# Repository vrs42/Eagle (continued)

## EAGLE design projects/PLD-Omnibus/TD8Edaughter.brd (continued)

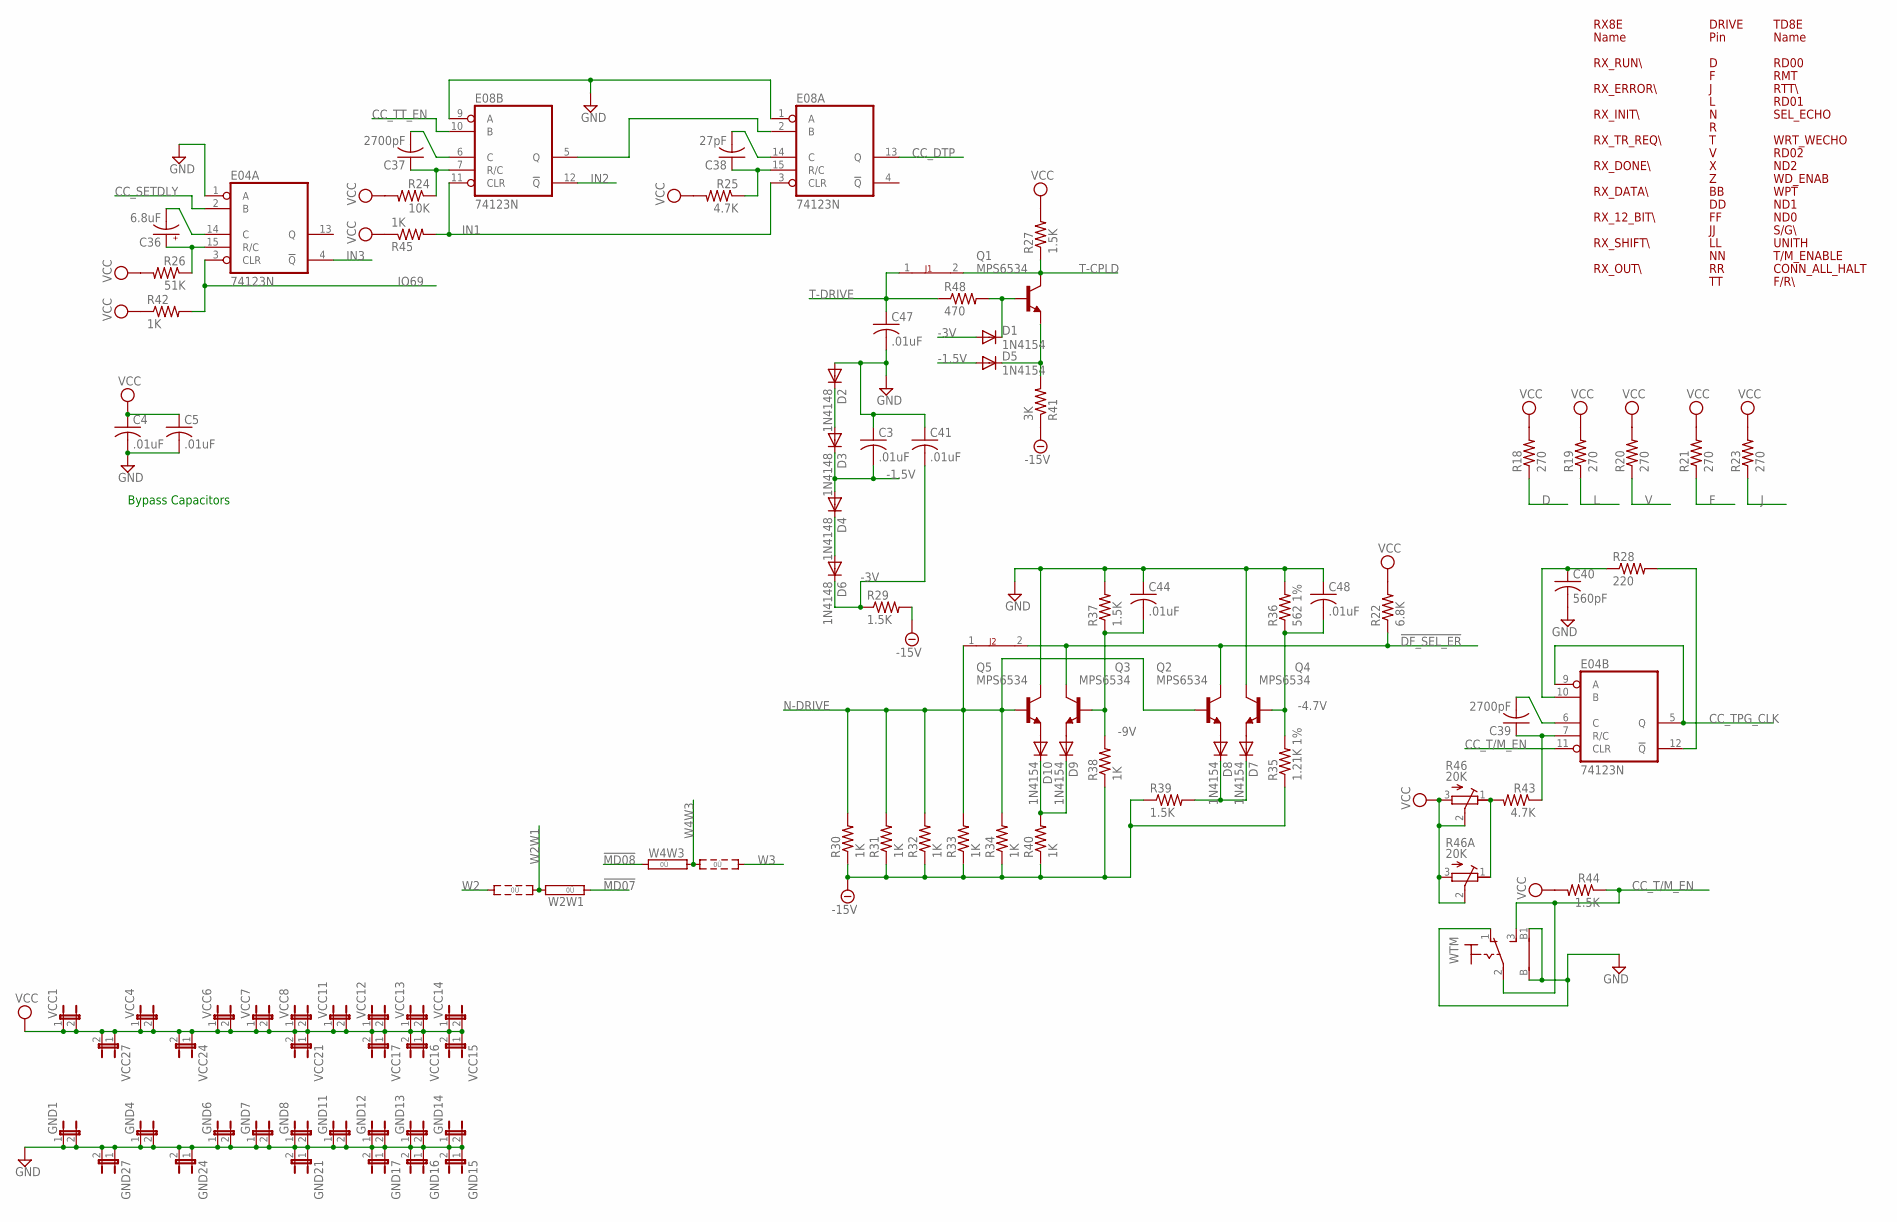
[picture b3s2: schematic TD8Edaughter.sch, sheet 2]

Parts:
C3, C4, C5, C41, C44, C47, C48: .01uF; C050-025X075
C36: 6.8uF; E12-8
C37, C39: 2700pF; C102-043X133
C38: 27pF; C050-025X075
C40: 560pF; C075-032X103
D1, D5, D7, D8, D9, D10: 1N4154; DO35-10
D2, D3, D4, D6: 1N4148; DO35-10
E04, E08: 74123N; DIL16
GND1, GND4, GND6, GND7, GND8, GND11, GND12, GND13, GND14, GND15, GND16, GND17, GND21, GND24, GND27: JP1E; JP1
J1, J2: JUMPER-NC; NC1
Q1, Q2, Q3, Q4, Q5: MPS6534; TO5
R18, R19, R20, R21, R23: 270; 0207/10
R22: 6.8K; 0207/10
R24: 10K; 0207/10
R25, R43: 4.7K; 0207/10
R26: 51K; 0207/10
R27, R29, R37, R39, R44: 1.5K; 0207/10
R28: 220; 0207/10
R30, R31, R32, R33, R34, R38, R40, R42, R45: 1K; 0207/10
R35: 1.21K 1%; 0207/15
R36: 562 1%; 0207/15
R41: 3K; 0207/10
R46: 20K; 3006Y
R46A: 20K; RTRIM3006P
R48: 470; 0207/10
VCC1, VCC4, VCC6, VCC7, VCC8, VCC11, VCC12, VCC13, VCC14, VCC15, VCC16, VCC17, VCC21, VCC24, VCC27: JP1E; JP1
W2W1, W4W3: 0R2; 0R2/10
WTM: 9070-1W

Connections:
!CC_TPG_CLK: C40.1, E04.10 (B), R28.1
!DF_SEL_ER: J2.2, Q2.3 (C), Q3.3 (C), R22.1; also elsewhere on the board
!MD07: W2W1.1; also elsewhere on the board
!MD08: W4W3.1; also elsewhere on the board
-1.5V: C3.2, D3.C, D4.A, D5.A
-3V: C41.2, D1.A, D6.C, R29.1
-4.7V: C48.2, Q4.2 (B), R35.2, R36.1
-9V: C44.2, Q3.2 (B), R37.1, R38.2
-15V: R29.2, R30.1, R31.1, R32.1, R33.1, R34.1, R35.1, R38.1, R39.1, R40.1, R41.1; also elsewhere on the board
CC_DTP: E08.13 (Q); also elsewhere on the board
CC_SETDLY: E04.2 (B); also elsewhere on the board
CC_T/M_EN: E04.11 (CLR), R44.1, WTM.2, WTM.3 (S); also elsewhere on the board
CC_TPG_CLK: E04.5 (Q), E04.9 (A); also elsewhere on the board
CC_TT_EN: E08.10 (B); also elsewhere on the board
D: R18.1; also elsewhere on the board
F: R21.1; also elsewhere on the board
GND: C3.1, C4.2, C5.2, C40.2, C41.1, C44.1, C47.2, C48.1, D2.A, E04.1 (A), E04.8 (GND), E08.1 (A), E08.8 (GND), E08.9 (A), GND1.1, GND1.2, GND4.1, GND4.2, GND6.1, GND6.2, GND7.1, GND7.2, GND8.1, GND8.2, GND11.1, GND11.2, GND12.1, GND12.2, GND13.1, GND13.2, GND14.1, GND14.2, GND15.1, GND15.2, GND16.1, GND16.2, GND17.1, GND17.2, GND21.1, GND21.2, GND24.1, GND24.2, GND27.1, GND27.2, Q4.3 (C), Q5.3 (C), R36.2, R37.2, WTM.1 (O), WTM.B, WTM.B1; also elsewhere on the board
IN1: E08.3 (CLR), E08.11 (CLR), R45.2; also elsewhere on the board
IN2: E08.12 (!Q); also elsewhere on the board
IN3: E04.4 (!Q); also elsewhere on the board
IO69: E04.3 (CLR), R42.2; also elsewhere on the board
J: R23.1; also elsewhere on the board
L: R19.1; also elsewhere on the board
unnamed: D1.C, Q1.2 (B), R48.2
unnamed: D5.C, Q1.1 (E), R41.2
unnamed: D2.C, D3.A
unnamed: D9.C, D10.C, R40.2
unnamed: D4.C, D6.A
unnamed: D10.A, Q5.1 (E)
unnamed: D9.A, Q3.1 (E)
unnamed: D8.A, Q2.1 (E)
unnamed: D7.A, Q4.1 (E)
unnamed: D7.C, D8.C, R39.2
unnamed: E08.2 (B), E08.5 (Q)
unnamed: C37.1, E08.7 (R/C), R24.1
unnamed: C38.1, E08.15 (R/C), R25.1
unnamed: C38.2, E08.14 (C)
unnamed: C37.2, E08.6 (C)
unnamed: C36.+, E04.15 (R/C), R26.1
unnamed: C36.-, E04.14 (C)
unnamed: C39.1, E04.7 (R/C), R43.1
unnamed: C39.2, E04.6 (C)
unnamed: R43.2, R46.1 (A), R46A.1 (E)
unnamed: E04.12 (!Q), R28.2
N-DRIVE: J2.1, Q2.2 (B), Q5.2 (B), R30.2, R31.2, R32.2, R33.2, R34.2; also elsewhere on the board
T-CPLD: J1.2, Q1.3 (C), R27.1; also elsewhere on the board
T-DRIVE: C47.1, J1.1, R48.1; also elsewhere on the board
V: R20.1; also elsewhere on the board
VCC: C4.1, C5.1, E04.16 (VCC), E08.16 (VCC), R18.2, R19.2, R20.2, R21.2, R22.2, R23.2, R24.2, R25.2, R26.2, R27.2, R42.1, R44.2, R45.1, R46.2 (S), R46.3 (E), R46A.2 (S), R46A.3 (A), VCC1.1, VCC1.2, VCC4.1, VCC4.2, VCC6.1, VCC6.2, VCC7.1, VCC7.2, VCC8.1, VCC8.2, VCC11.1, VCC11.2, VCC12.1, VCC12.2, VCC13.1, VCC13.2, VCC14.1, VCC14.2, VCC15.1, VCC15.2, VCC16.1, VCC16.2, VCC17.1, VCC17.2, VCC21.1, VCC21.2, VCC24.1, VCC24.2, VCC27.1, VCC27.2; also elsewhere on the board
W2: W2W1.3; also elsewhere on the board
W2W1: W2W1.2; also elsewhere on the board
W3: W4W3.3; also elsewhere on the board
W4W3: W4W3.2; also elsewhere on the board

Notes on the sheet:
Bypass Capacitors
DRIVE
Pin
RD00
RMT
RTT\\
RD01
SEL_ECHO
WRT_WECHO
RD02
ND2
WD_ENAB
WPT
ND1
ND0
S/G\\
UNITH
T/M_ENABLE
CONN_ALL_HALT
F/R\\
TD8E
Name
RX_RUN\\
RX_ERROR\\
RX_INIT\\
RX_TR_REQ\\
RX_DONE\\
RX_DATA\\
RX_12_BIT\\
RX_SHIFT\\
RX_OUT\\
RX8E

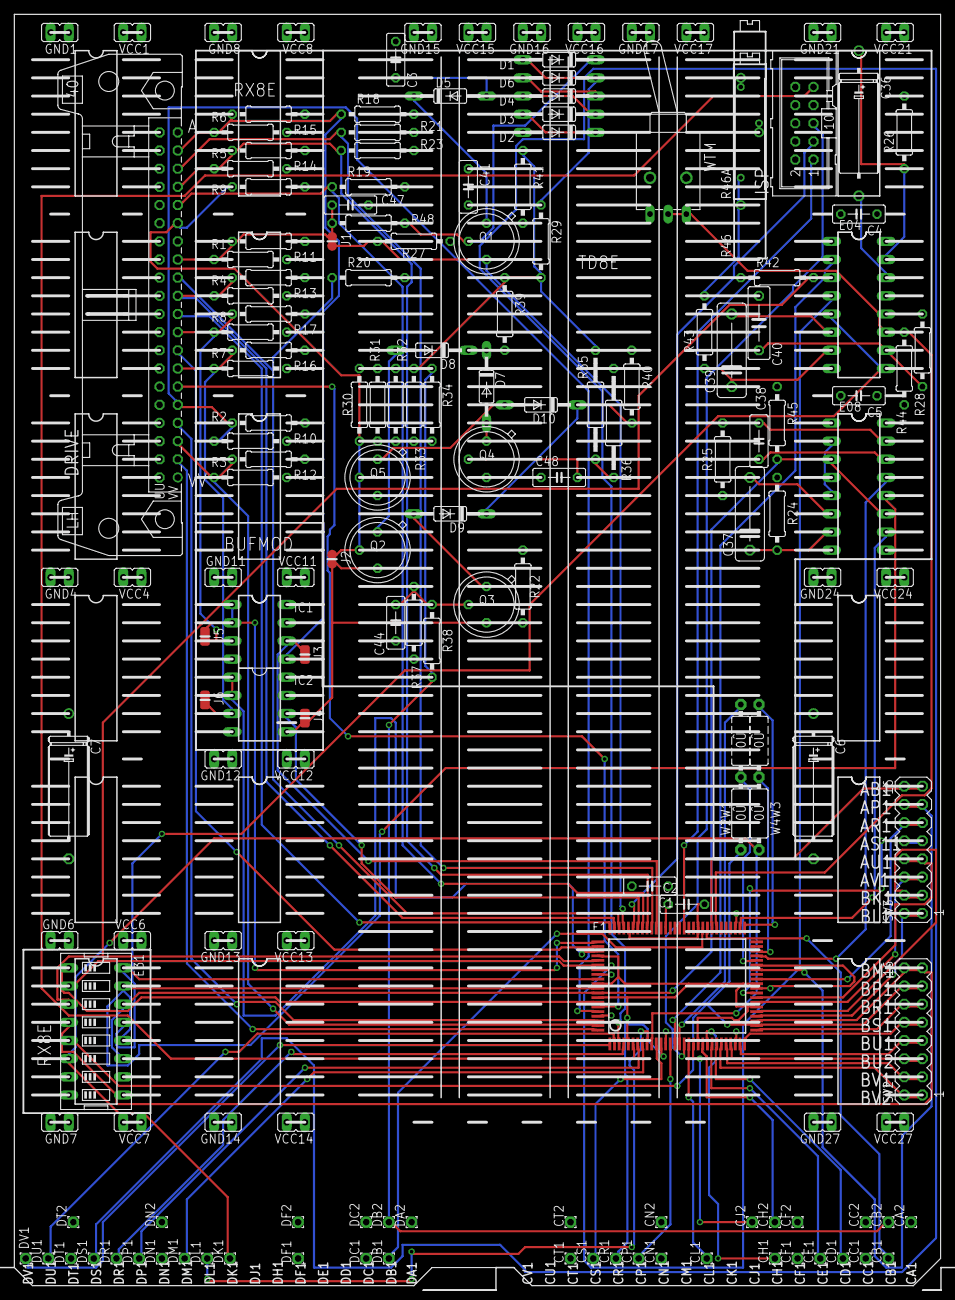
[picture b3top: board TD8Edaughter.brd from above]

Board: 4 copper layers, 129.5 x 177.8 mm, 167 parts (0 on the bottom side), 106 nets.

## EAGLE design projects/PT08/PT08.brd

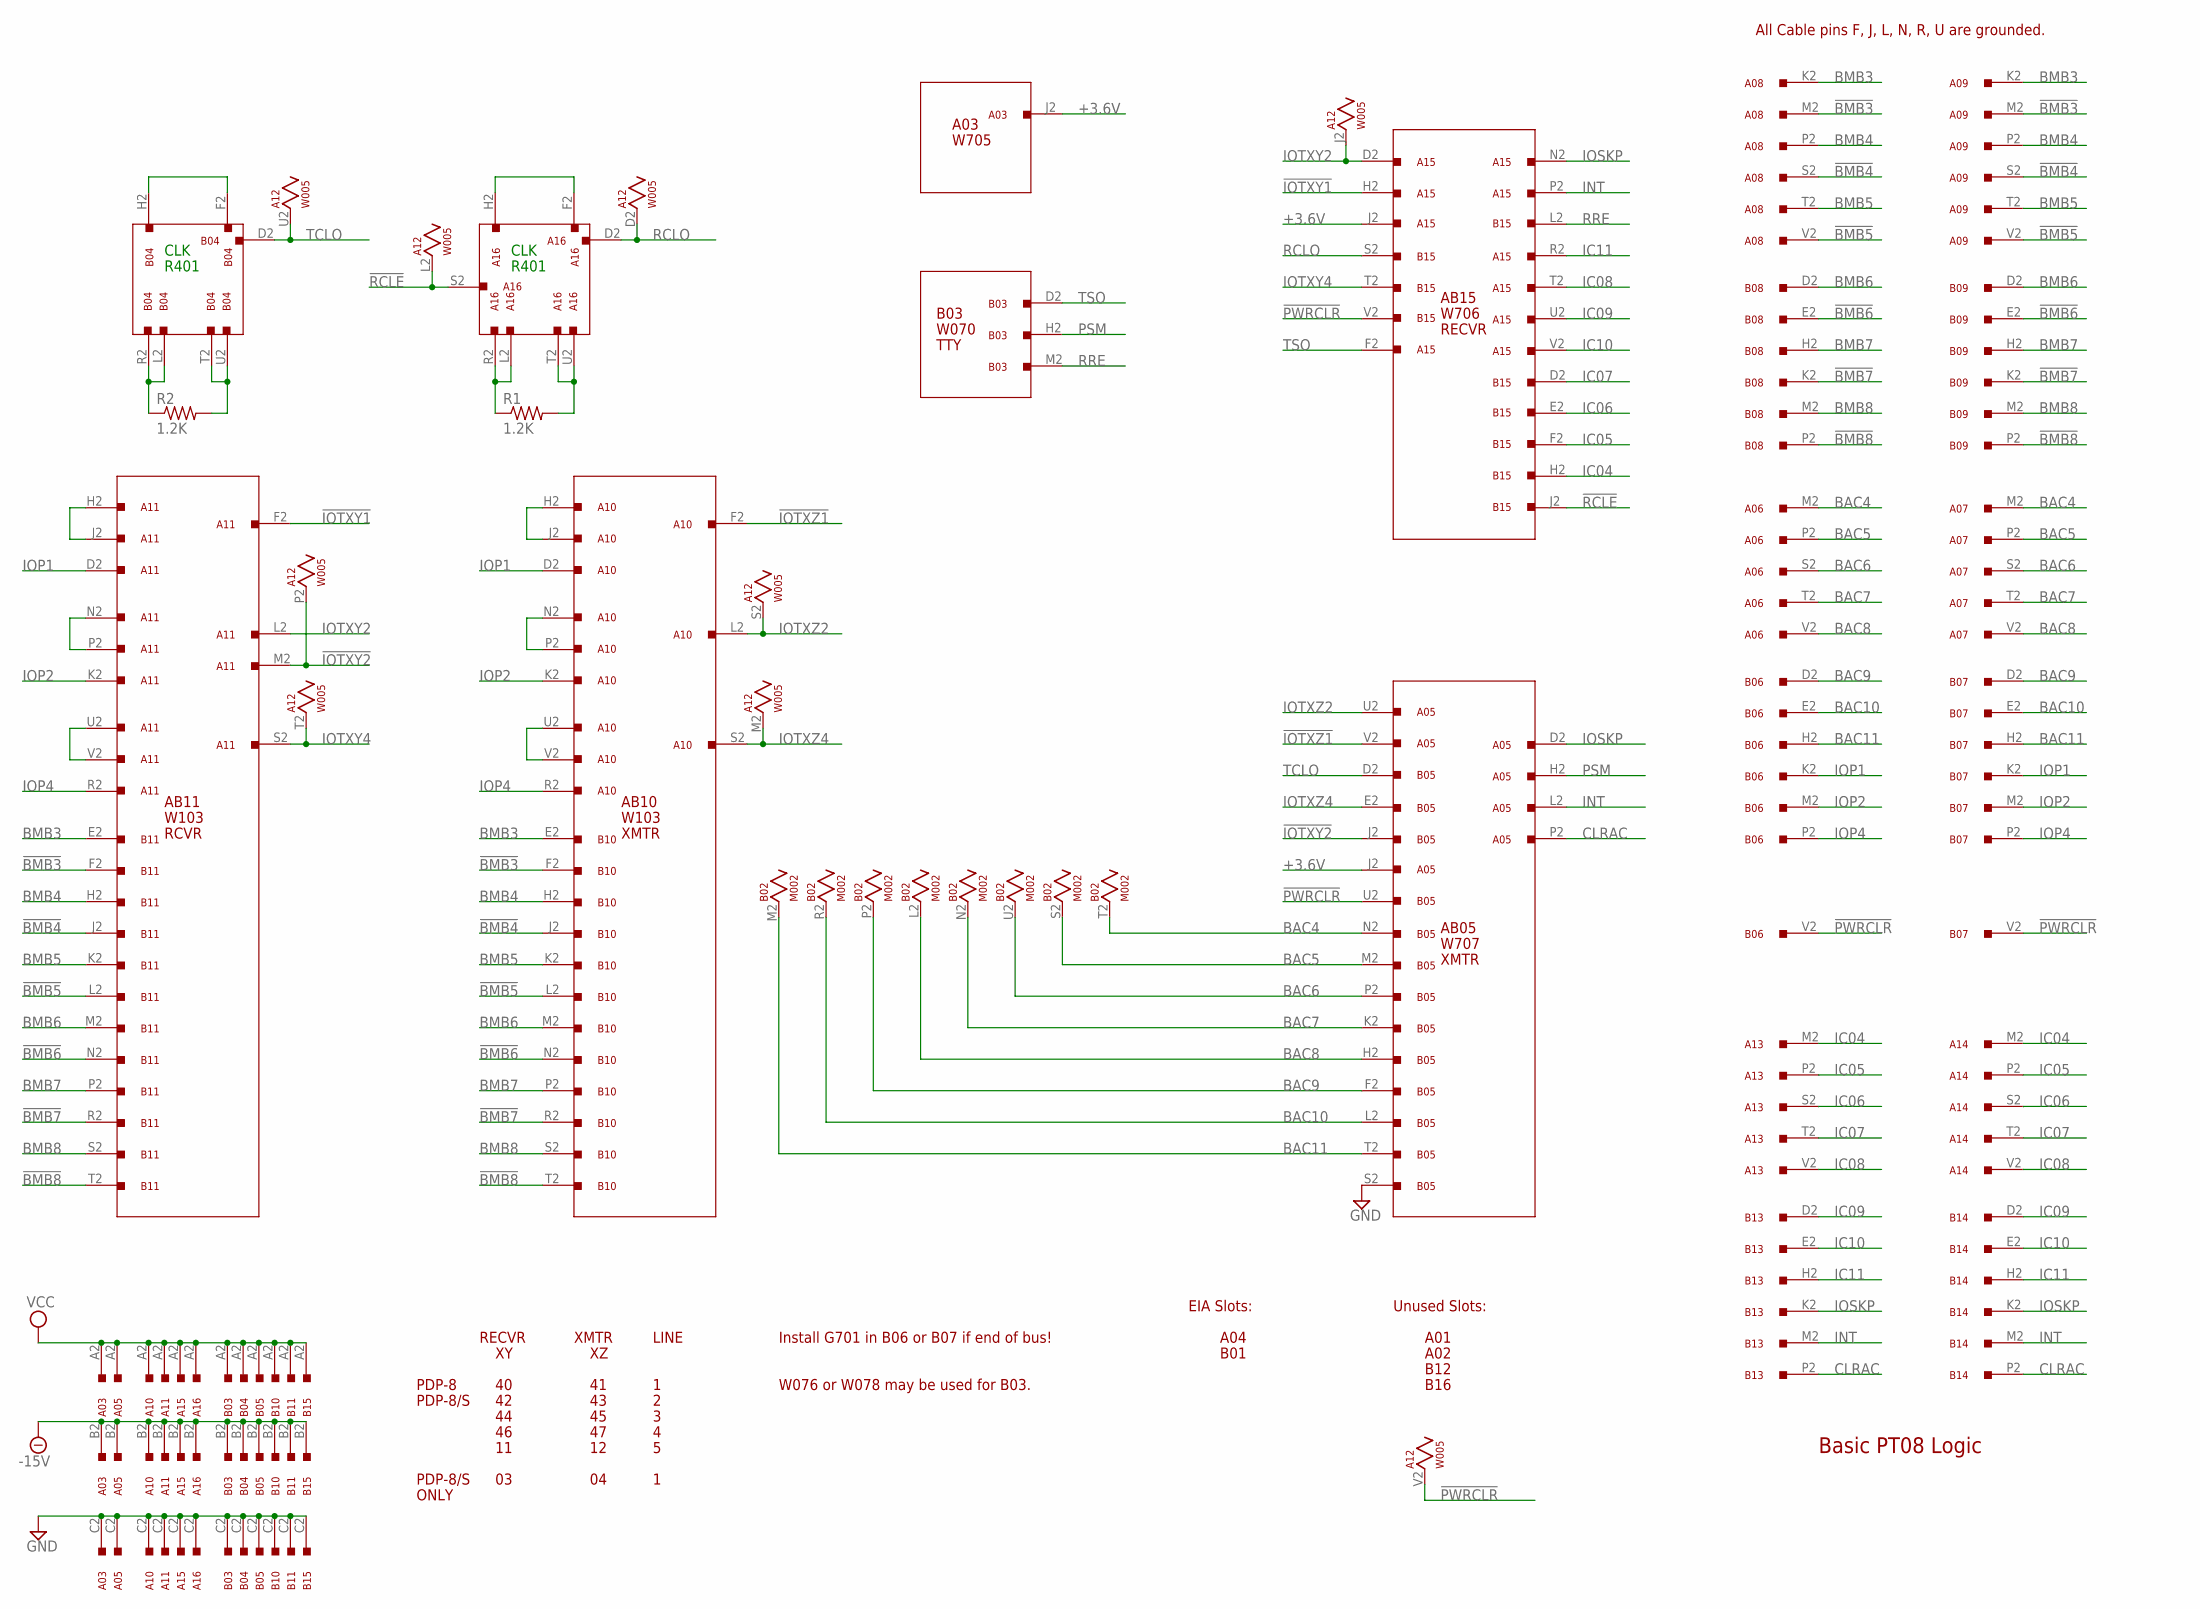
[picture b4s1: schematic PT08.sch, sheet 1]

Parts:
A01, A02: H807
A03: W705; H807
A05: W707; H807
A06, A07, A08, A09, A13, A14: W011; H807
A10, A11: W103; H807
A12: W005; H807
A15: W706; H807
A16: R401; H807
B02: M002; H807
B03: W076; H807
B04: R401; H807
B05: W707; H807
B06, B07, B08, B09, B13, B14: W011; H807
B10, B11: W103; H807
B12, B16: H807
B15: W706; H807
R1, R2: 1.2K; 0207/10

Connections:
!BMB3: A08.M2, A09.M2, B10.F2, B11.F2
!BMB4: A08.S2, A09.S2, B10.J2, B11.J2
!BMB5: A08.V2, A09.V2, B10.L2, B11.L2
!BMB6: B08.E2, B09.E2, B10.N2, B11.N2
!BMB7: B08.K2, B09.K2, B10.R2, B11.R2
!BMB8: B08.P2, B09.P2, B10.T2, B11.T2
!IOTXY1: A11.F2, A15.H2
!IOTXY2: A11.M2, A12.P2, B05.J2
!IOTXZ1: A05.V2, A10.F2
!PWRCLR: A12.V2, B05.U2, B06.V2, B07.V2, B15.V2
!RCLE: A12.L2, A16.S2, B15.J2
+3.6V: A03.J2, A05.J2, A15.J2
-15V: A03.B2, A05.B2, A10.B2, A11.B2, A12.B2 (-15V), A15.B2, A16.B2, B03.B2, B04.B2, B05.B2, B10.B2, B11.B2, B15.B2; also elsewhere on the board
BAC4: A06.M2, A07.M2, B02.T2, B05.N2
BAC5: A06.P2, A07.P2, B02.S2, B05.M2
BAC6: A06.S2, A07.S2, B02.U2, B05.P2
BAC7: A06.T2, A07.T2, B02.N2, B05.K2
BAC8: A06.V2, A07.V2, B02.L2, B05.H2
BAC9: B02.P2, B05.F2, B06.D2, B07.D2
BAC10: B02.R2, B05.L2, B06.E2, B07.E2
BAC11: B02.M2, B05.T2, B06.H2, B07.H2
BMB3: A08.K2, A09.K2, B10.E2, B11.E2
BMB4: A08.P2, A09.P2, B10.H2, B11.H2
BMB5: A08.T2, A09.T2, B10.K2, B11.K2
BMB6: B08.D2, B09.D2, B10.M2, B11.M2
BMB7: B08.H2, B09.H2, B10.P2, B11.P2
BMB8: B08.M2, B09.M2, B10.S2, B11.S2
CLRAC: A05.P2, B13.P2, B14.P2
GND: A03.C2, A05.C2, A06.C2 (GND), A06.F2 (GND), A06.J2 (GND), A06.L2 (GND), A06.N2 (GND), A06.R2 (GND), A06.U2 (GND), A07.C2 (GND), A07.F2 (GND), A07.J2 (GND), A07.L2 (GND), A07.N2 (GND), A07.R2 (GND), A07.U2 (GND), A08.C2 (GND), A08.F2 (GND), A08.J2 (GND), A08.L2 (GND), A08.N2 (GND), A08.R2 (GND), A08.U2 (GND), A09.C2 (GND), A09.F2 (GND), A09.J2 (GND), A09.L2 (GND), A09.N2 (GND), A09.R2 (GND), A09.U2 (GND), A10.C2, A11.C2, A12.C2 (GND), A13.C2 (GND), A13.F2 (GND), A13.J2 (GND), A13.L2 (GND), A13.N2 (GND), A13.R2 (GND), A13.U2 (GND), A14.C2 (GND), A14.F2 (GND), A14.J2 (GND), A14.L2 (GND), A14.N2 (GND), A14.R2 (GND), A14.U2 (GND), A15.C2, A16.C2, B02.C2 (GND), B03.C2, B04.C2, B05.C2, B05.S2, B06.C2 (GND), B06.F2 (GND), B06.J2 (GND), B06.L2 (GND), B06.N2 (GND), B06.R2 (GND), B06.U2 (GND), B07.C2 (GND), B07.F2 (GND), B07.J2 (GND), B07.L2 (GND), B07.N2 (GND), B07.R2 (GND), B07.U2 (GND), B08.C2 (GND), B08.F2 (GND), B08.J2 (GND), B08.L2 (GND), B08.N2 (GND), B08.R2 (GND), B08.U2 (GND), B09.C2 (GND), B09.F2 (GND), B09.J2 (GND), B09.L2 (GND), B09.N2 (GND), B09.R2 (GND), B09.U2 (GND), B10.C2, B11.C2, B13.C2 (GND), B13.F2 (GND), B13.J2 (GND), B13.L2 (GND), B13.N2 (GND), B13.R2 (GND), B13.U2 (GND), B14.C2 (GND), B14.F2 (GND), B14.J2 (GND), B14.L2 (GND), B14.N2 (GND), B14.R2 (GND), B14.U2 (GND), B15.C2; also elsewhere on the board
IC04: A13.M2, A14.M2, B15.H2
IC05: A13.P2, A14.P2, B15.F2
IC06: A13.S2, A14.S2, B15.E2
IC07: A13.T2, A14.T2, B15.D2
IC08: A13.V2, A14.V2, A15.T2
IC09: A15.U2, B13.D2, B14.D2
IC10: A15.V2, B13.E2, B14.E2
IC11: A15.R2, B13.H2, B14.H2
INT: A05.L2, A15.P2, B13.M2, B14.M2
IOP1: A10.D2, A11.D2, B06.K2, B07.K2
IOP2: A10.K2, A11.K2, B06.M2, B07.M2
IOP4: A10.R2, A11.R2, B06.P2, B07.P2
IOSKP: A05.D2, A15.N2, B13.K2, B14.K2
IOTXY2: A11.L2, A12.J2, A15.D2
IOTXY4: A11.S2, A12.T2, B15.T2
IOTXZ2: A05.U2, A10.L2, A12.S2
IOTXZ4: A10.S2, A12.M2, B05.E2
unnamed: A10.U2, A10.V2
unnamed: A16.F2, A16.H2
unnamed: A16.L2, A16.R2, R1.1
unnamed: A16.T2, A16.U2, R1.2
unnamed: A10.H2, A10.J2
unnamed: B04.F2, B04.H2
unnamed: B04.L2, B04.R2, R2.1
unnamed: B04.T2, B04.U2, R2.2
unnamed: A11.U2, A11.V2
unnamed: A11.H2, A11.J2
unnamed: A10.N2, A10.P2
unnamed: A11.N2, A11.P2
PSM: A05.H2, B03.H2; also elsewhere on the board
RCLO: A12.D2, A16.D2, B15.S2
RRE: B03.M2, B15.L2
TCLO: A12.U2, B04.D2, B05.D2
TSO: A15.F2, B03.D2; also elsewhere on the board
VCC: A03.A2, A05.A2, A10.A2, A11.A2, A12.A2 (VCC), A15.A2, A16.A2, B02.A2 (VCC), B03.A2, B04.A2, B05.A2, B10.A2, B11.A2, B15.A2; also elsewhere on the board

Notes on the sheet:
R401
CLK
AB11
RCVR
AB10
XMTR
AB05
W707
W103
W705
A03
AB15
RECVR
W706
B03
W070
TTY
Unused Slots:
Basic PT08 Logic
LINE
PDP-8
PDP-8/S
ONLY
Install G701 in B06 or B07 if end of bus!
All Cable pins F, J, L, N, R, U are grounded.
W076 or W078 may be used for B03.
EIA Slots:
B01
A04

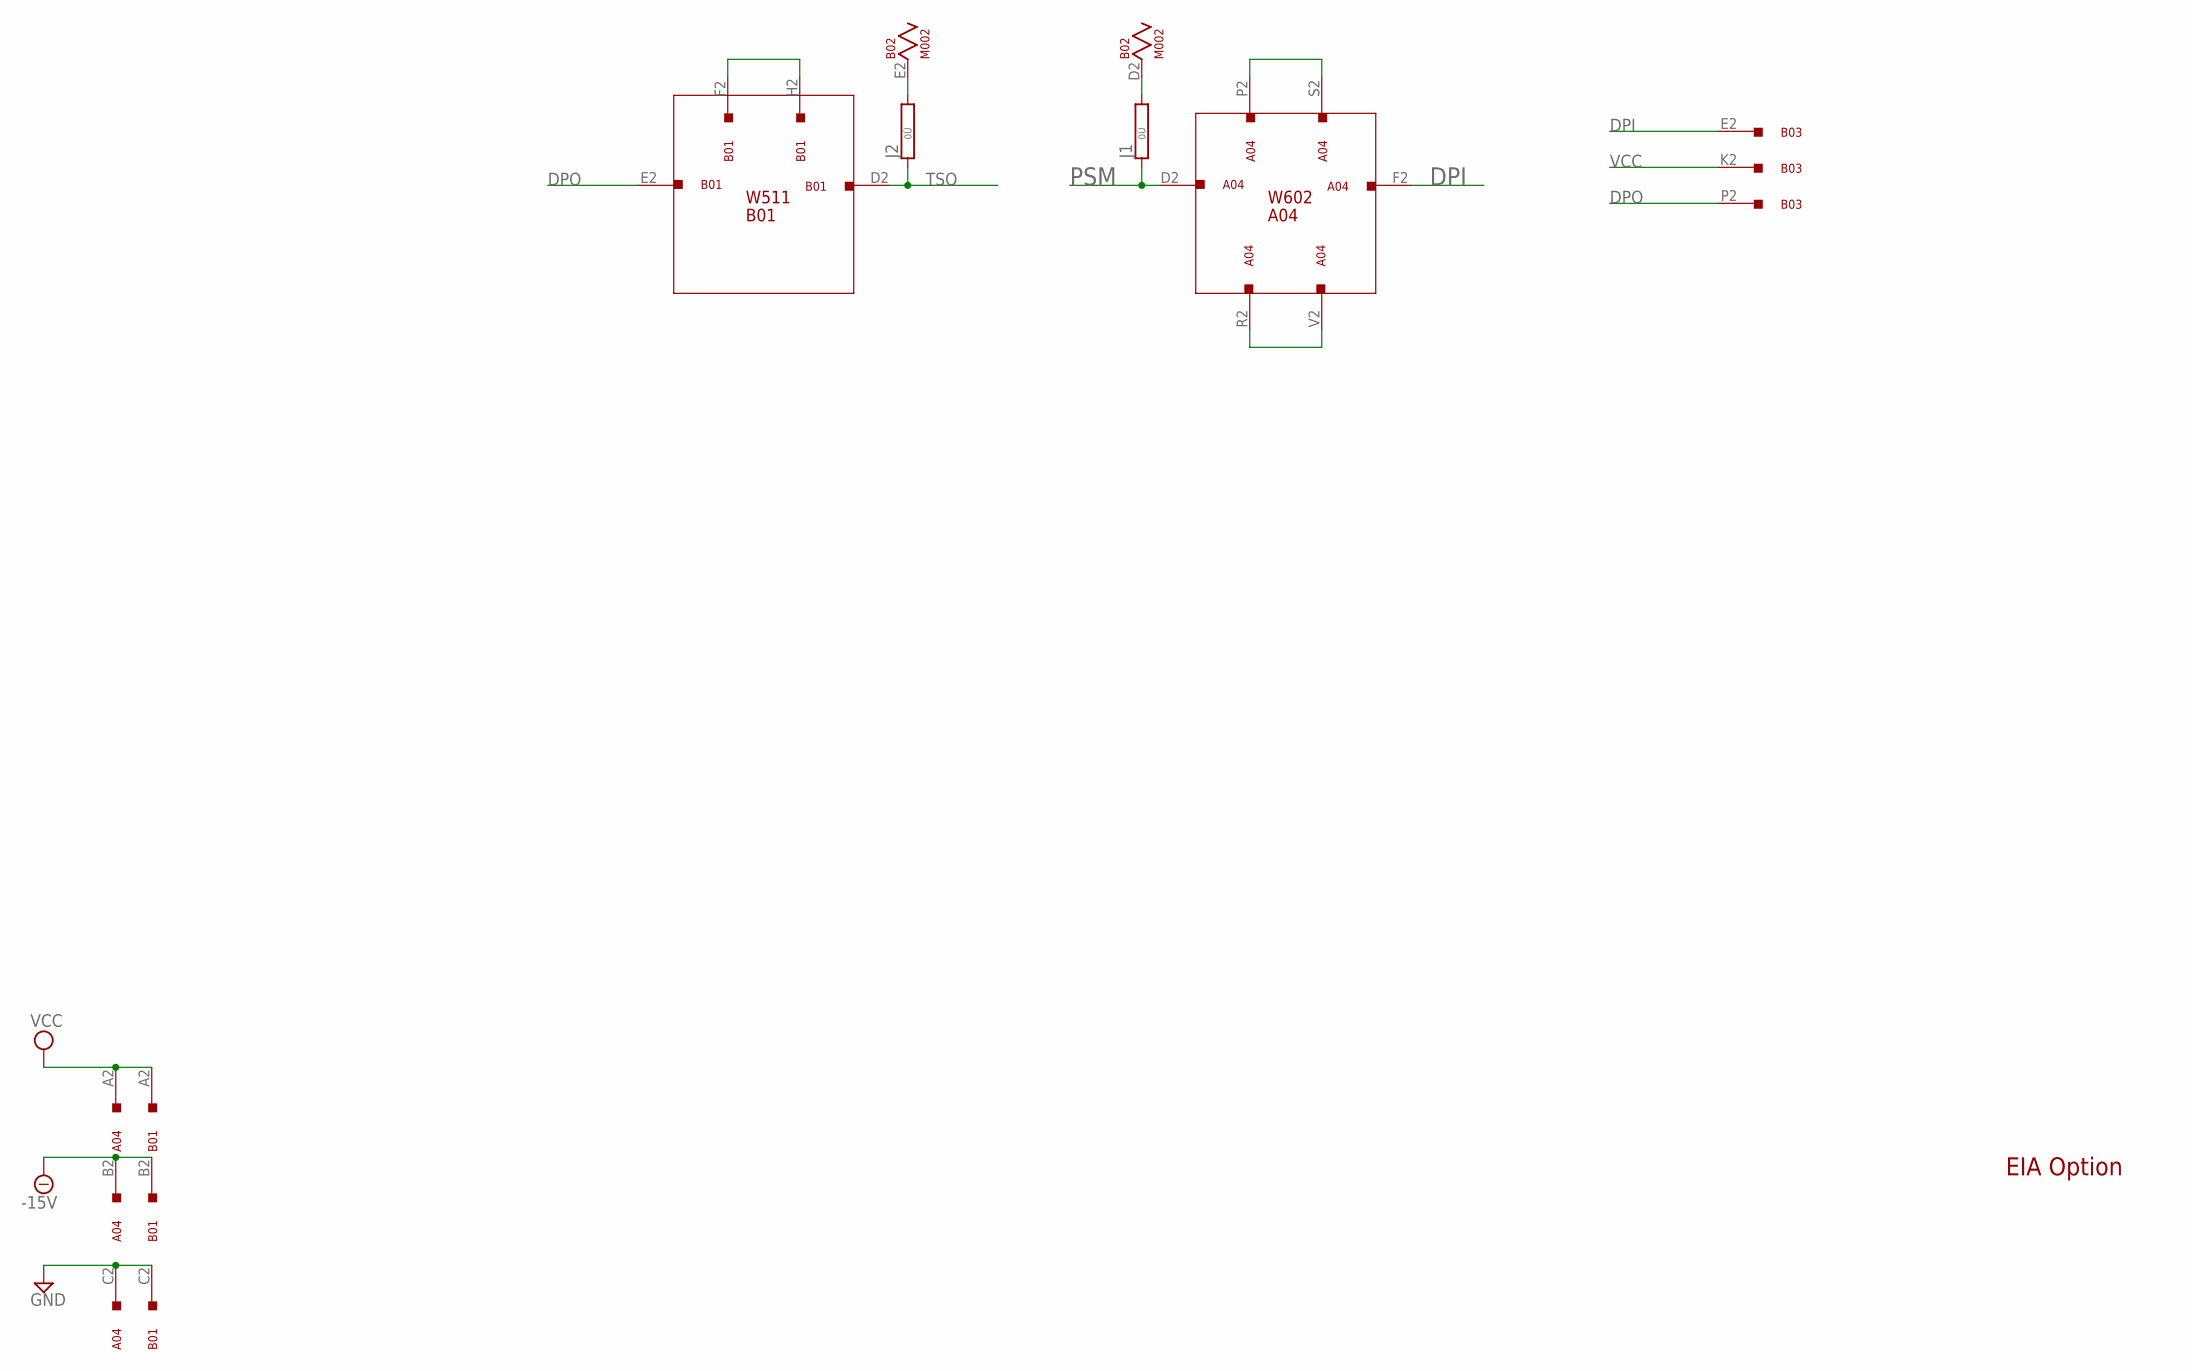
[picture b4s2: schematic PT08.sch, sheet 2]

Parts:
A04: W602; H807
B01: W511; H807
B02: M002; H807
B03: W076; H807
J1, J2: 0R; 0R/10

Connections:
-15V: A04.B2, B01.B2; also elsewhere on the board
DPI: A04.F2, B03.E2
DPO: B01.E2, B03.P2
GND: A04.C2, B01.C2, B02.C2 (GND); also elsewhere on the board
unnamed: A04.P2, A04.S2
unnamed: A04.R2, A04.V2
unnamed: B02.D2, J1.2
unnamed: B01.F2, B01.H2
unnamed: B02.E2, J2.2
PSM: A04.D2, J1.1; also elsewhere on the board
TSO: B01.D2, J2.1; also elsewhere on the board
VCC: A04.A2, B01.A2, B02.A2 (VCC), B03.K2; also elsewhere on the board

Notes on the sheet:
EIA Option
W602
A04
B01
W511

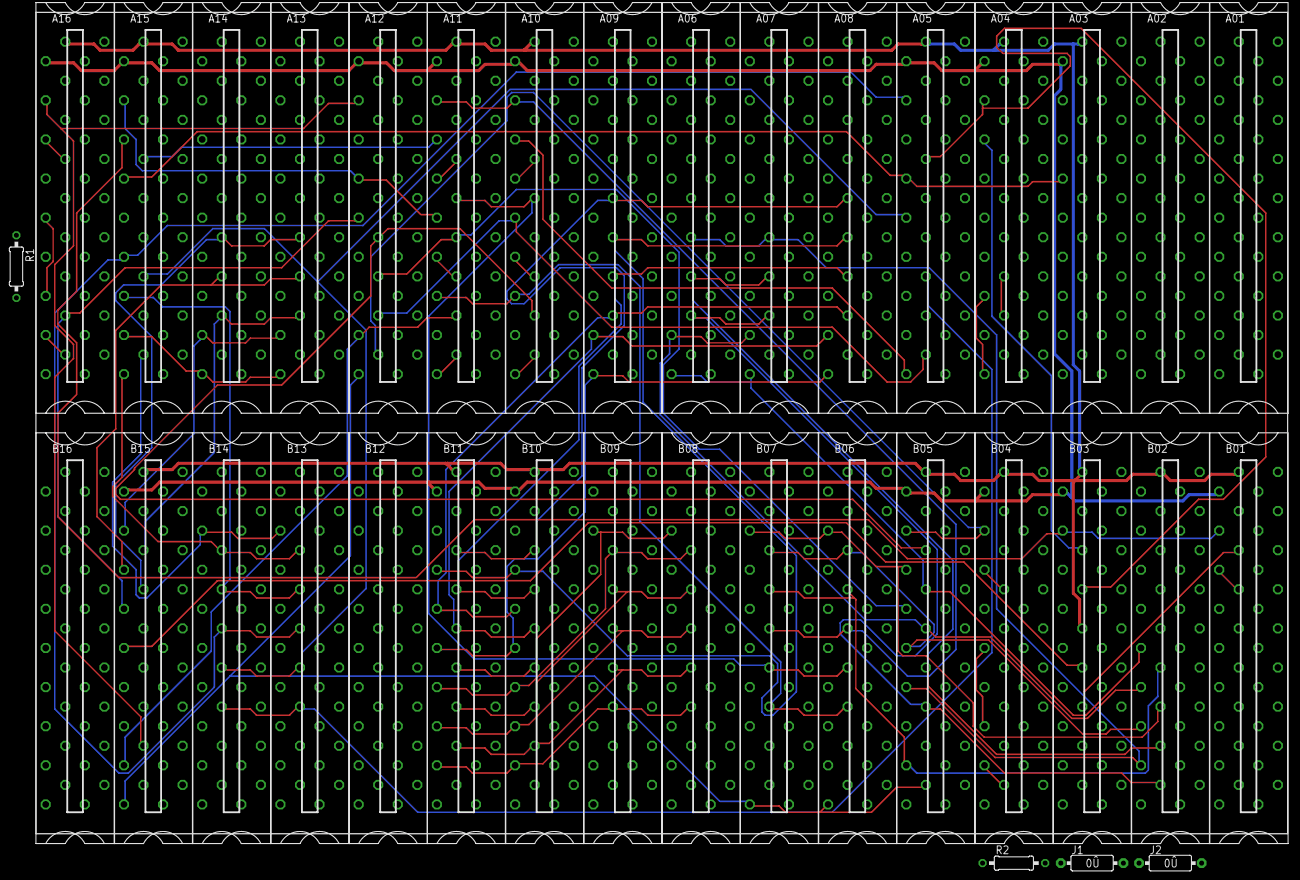
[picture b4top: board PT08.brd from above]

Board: 3 copper layers, 203.2 x 133.3 mm, 36 parts (0 on the bottom side), 71 nets.

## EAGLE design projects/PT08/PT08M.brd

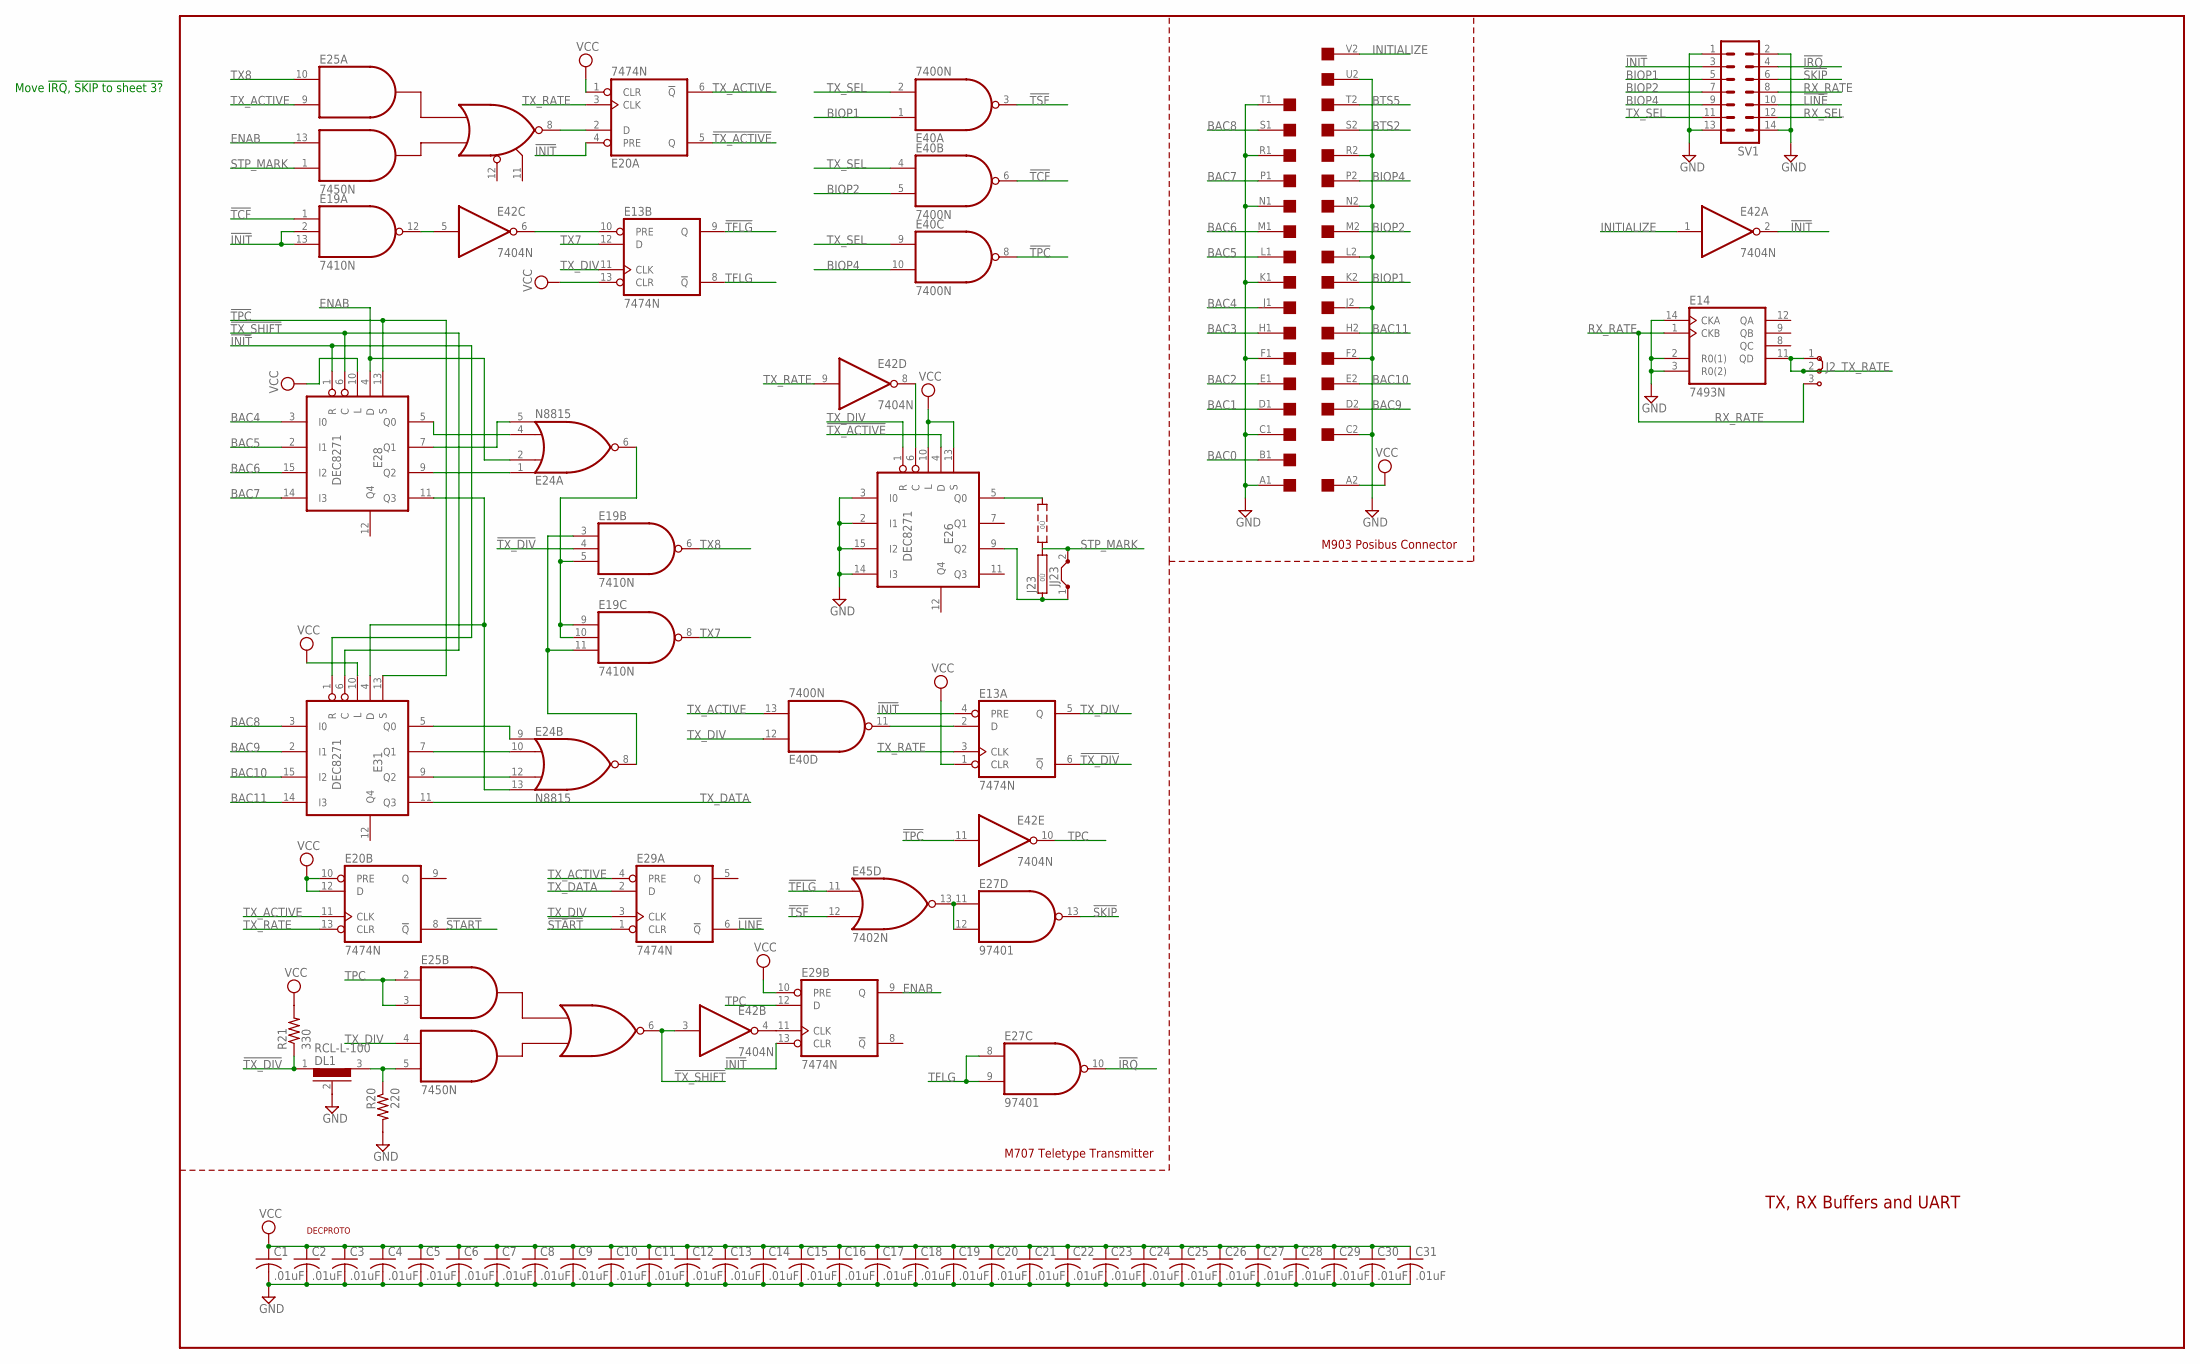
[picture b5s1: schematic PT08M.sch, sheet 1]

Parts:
C1, C2, C3, C4, C5, C6, C7, C8, C9, C10, C11, C12, C13, C14, C15, C16, C17, C18, C19, C20, C21, C22, C23, C24, C25, C26, C27, C28, C29, C30, C31: .01uF; C050-025X075
DL1: RCL-L-100; RCL-L-00-05
E13, E20, E29: 7474N; DIL14
E14: 7493N; DIL14
E19: 7410N; DIL14
E24: N8815; DIL14
E25: 7450N; DIL14
E26, E28, E31: DEC8271; DIL16
E27: 97401; DIL14
E40: 7400N; DIL14
E42: 7404N; DIL14
E45: 7402N; DIL14
J2: J2X2MM; 04C
J23: 0R2; 0R2/10
JJ23: J10MM; 10
N14: EDGE-2CONNECTOR; EDGE-CON2
R20: 220; 0207/10
R21: 330; 0207/10
SV1: ML14L
U$2: DECPROTO; DECPROTO111

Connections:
!INIT: E13.4 (PRE), E19.2 (I1), E19.13 (I2), E20.4 (PRE), E28.1 (R), E29.13 (CLR), E31.1 (R), E42.2 (O), SV1.3; also elsewhere on the board
!IRQ: E27.10 (O), SV1.4; also elsewhere on the board
!LINE: E29.6 (!Q), SV1.10; also elsewhere on the board
!SKIP: E27.13 (O), SV1.6; also elsewhere on the board
!START: E20.8 (!Q), E29.1 (CLR)
!TCF: E19.1 (I0), E40.6 (O)
!TFLG: E13.9 (Q), E45.11 (I0)
!TPC: E28.13 (S), E31.13 (S), E40.8 (O), E42.11 (I)
!TSF: E40.3 (O), E45.12 (I1)
!TX_ACTIVE: E20.5 (Q), E26.4 (D)
!TX_DIV: DL1.1, E13.6 (!Q), E19.4 (I1), R21.1
!TX_SHIFT: E25.6 (O), E28.6 (C), E31.6 (C), E42.3 (I)
BAC0: N14.B1
BAC1: N14.D1
BAC2: N14.E1
BAC3: N14.H1
BAC4: E28.3 (I0), N14.J1
BAC5: E28.2 (I1), N14.L1
BAC6: E28.15 (I2), N14.M1
BAC7: E28.14 (I3), N14.P1
BAC8: E31.3 (I0), N14.S1
BAC9: E31.2 (I1), N14.D2
BAC10: E31.15 (I2), N14.E2
BAC11: E31.14 (I3), N14.H2
BIOP1: E40.1 (I0), N14.K2, SV1.5; also elsewhere on the board
BIOP2: E40.5 (I1), N14.M2, SV1.7; also elsewhere on the board
BIOP4: E40.10 (I1), N14.P2, SV1.9; also elsewhere on the board
BTS2: N14.S2
BTS5: N14.T2
ENAB: E24.2 (I1), E25.13 (I3), E28.4 (D), E29.9 (Q)
GND: C1.2, C2.2, C3.2, C4.2, C5.2, C6.2, C7.2, C8.2, C9.2, C10.2, C11.2, C12.2, C13.2, C14.2, C15.2, C16.2, C17.2, C18.2, C19.2, C20.2, C21.2, C22.2, C23.2, C24.2, C25.2, C26.2, C27.2, C28.2, C29.2, C30.2, C31.2, DL1.2, E13.7 (GND), E14.2 (R0(1)), E14.3 (R0(2)), E14.10 (GND), E14.14 (CKA), E19.7 (GND), E20.7 (GND), E24.7 (GND), E25.7 (GND), E26.2 (I1), E26.3 (I0), E26.8 (GND), E26.14 (I3), E26.15 (I2), E27.7 (GND), E28.8 (GND), E29.7 (GND), E31.8 (GND), E40.7 (GND), E42.7 (GND), E45.7 (GND), N14.A1, N14.C1, N14.C2, N14.F1, N14.F2, N14.J2, N14.K1, N14.L2, N14.N1, N14.N2, N14.R1, N14.R2, N14.T1, N14.U2, R20.2, SV1.1, SV1.2, SV1.13, SV1.14; also elsewhere on the board
INITIALIZE: E42.1 (I), N14.V2
unnamed: E19.12 (O), E42.5 (I)
unnamed: E13.10 (PRE), E42.6 (O)
unnamed: E24.1 (I0), E28.9 (Q2)
unnamed: E24.4 (I2), E28.5 (Q0)
unnamed: E24.13 (I3), E28.11 (Q3), E31.4 (D)
unnamed: E24.5 (I3), E28.7 (Q1)
unnamed: E24.9 (I0), E31.5 (Q0)
unnamed: E24.10 (I1), E31.7 (Q1)
unnamed: E24.12 (I2), E31.9 (Q2)
unnamed: E19.3 (I0), E19.11 (I2), E24.8 (O)
unnamed: E19.5 (I2), E19.9 (I0), E19.10 (I1), E24.6 (O)
unnamed: E13.2 (D), E40.11 (O)
unnamed: E29.11 (CLK), E42.4 (O)
unnamed: DL1.3, E25.5 (I4), R20.1
unnamed: E20.2 (D), E25.8 (O)
unnamed: E26.9 (Q2), J23.1, JJ23.1
unnamed: E26.6 (C), E42.8 (O)
unnamed: E26.5 (Q0), J23.3
RX_RATE: E14.1 (CKB), J2.3, SV1.8; also elsewhere on the board
RX_SEL: SV1.12; also elsewhere on the board
STP_MARK: E25.1 (I4), J23.2, JJ23.2
TFLG: E13.8 (!Q), E27.8 (I0), E27.9 (I1)
TPC: E25.2 (I1), E25.3 (I2), E29.12 (D), E42.10 (O)
TSKP: E27.11 (I0), E27.12 (I1), E45.13 (O)
TX7: E13.12 (D), E19.8 (O)
TX8: E19.6 (O), E25.10 (I1)
TX_ACTIVE: E20.6 (!Q), E20.11 (CLK), E25.9 (I2), E29.4 (PRE), E40.13 (I1)
TX_DATA: E29.2 (D), E31.11 (Q3)
TX_DIV: E13.5 (Q), E13.11 (CLK), E25.4 (I3), E26.1 (R), E29.3 (CLK), E40.12 (I0)
TX_RATE: E13.3 (CLK), E14.11 (QD), E20.3 (CLK), E20.13 (CLR), E42.9 (I), J2.1, J2.2
TX_SEL: E40.2 (I1), E40.4 (I0), E40.9 (I0), SV1.11; also elsewhere on the board
VCC: C1.1, C2.1, C3.1, C4.1, C5.1, C6.1, C7.1, C8.1, C9.1, C10.1, C11.1, C12.1, C13.1, C14.1, C15.1, C16.1, C17.1, C18.1, C19.1, C20.1, C21.1, C22.1, C23.1, C24.1, C25.1, C26.1, C27.1, C28.1, C29.1, C30.1, C31.1, E13.1 (CLR), E13.13 (CLR), E13.14 (VCC), E14.5 (VCC), E19.14 (VCC), E20.1 (CLR), E20.10 (PRE), E20.12 (D), E20.14 (VCC), E24.14 (VCC), E25.14 (VCC), E26.10 (L), E26.13 (S), E26.16 (VCC), E27.14 (VCC), E28.10 (L), E28.16 (VCC), E29.10 (PRE), E29.14 (VCC), E31.10 (L), E31.16 (VCC), E40.14 (VCC), E42.14 (VCC), E45.14 (VCC), N14.A2, R21.2; also elsewhere on the board

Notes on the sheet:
TX, RX Buffers and UART
M707 Teletype Transmitter
M903 Posibus Connector
Move !IRQ, !SKIP to sheet 3?
